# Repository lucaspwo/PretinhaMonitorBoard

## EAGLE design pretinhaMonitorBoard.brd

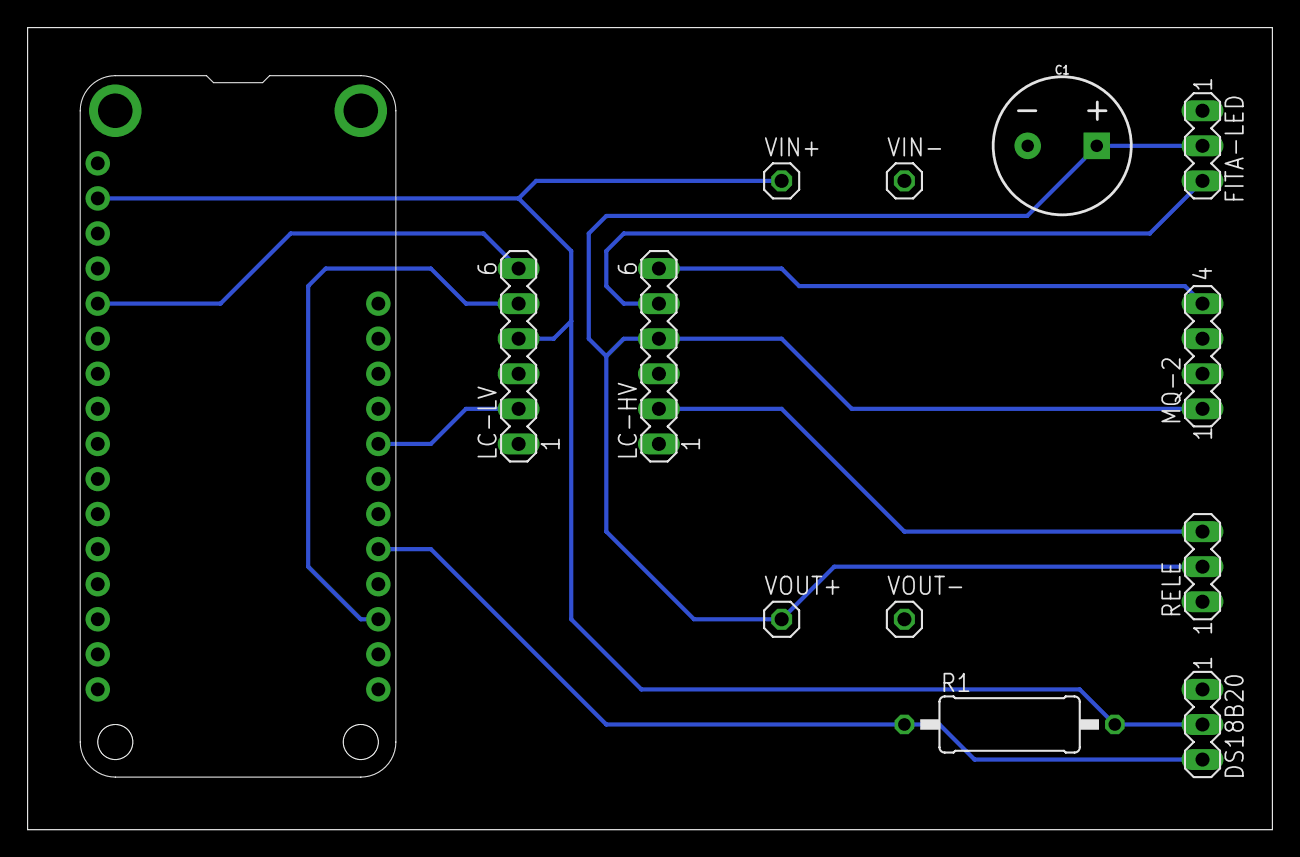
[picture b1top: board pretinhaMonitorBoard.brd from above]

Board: 2 copper layers, 90.2 x 58.1 mm, 13 parts (0 on the bottom side), 10 nets.

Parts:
C1: 1mF; CPOL-RADIAL-5MM-10MM
DS18B20: MA03-1
FITA-LED: MA03-1
LC-HV: MA06-1
LC-LV: MA06-1
MESH: FEATHERWING_NODIM; FEATHERWING_DIM
MQ-2: MA04-1
R1: 0411/15
RELE: MA03-1
VIN+: 1X01
VIN-: 1X01
VOUT+: 1X01
VOUT-: 1X01

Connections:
3V3: DS18B20.2, LC-LV.4, MESH.2, R1.2, VIN+.1
5V: C1.+, FITA-LED.2, LC-HV.4, MQ-2.1, RELE.2, VOUT+.1
A0: LC-LV.6, MESH.5
AOUT: LC-HV.6, MQ-2.4
D2: LC-LV.5, MESH.19
D4: DS18B20.3, MESH.21, R1.1
D7: LC-LV.2, MESH.24
GND: C1.-, DS18B20.1, FITA-LED.1, LC-HV.3, LC-LV.3, MESH.4, MQ-2.2, RELE.1, VIN-.1, VOUT-.1
LED: FITA-LED.3, LC-HV.5
RELE: LC-HV.2, RELE.3

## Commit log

2019-01-22 add pin to control camera
2019-01-30 add adafruit.lbr

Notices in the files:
parts and their libraries:
SparkFun-Capacitors: Licensing: Creative Commons ShareAlike 4.0 International - https://creativecommons.org/licenses/by-sa/4.0
